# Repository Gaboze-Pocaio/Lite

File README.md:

# Gaboze Lite Edition
Gaboze Lite is an even more no frills version of the Game Boy Pocket and Raspberry Pi Zero.

## What Did We Do?

* [x] Lakka Only Release *(You Can Still Have RetroPie)*
* [x] TP4056 Module Removed for more efficient Texs Instruments
* [x] 5V Power Rail
* [x] Full USB OTG Support
* [x] New Button Library With Better Actuation
* [x] Two Buttons Only

## Why Did We Do This

Well, we slimmed it down to a two button build (you can always wire more on your own). After market evaluation, and to keep costs lower.

## Preview

| Top  | Bottom |
| ---- | ------ |
|      |        |

## More Soon
> Stay Up To Date

* [x] Be Sure To **Watch** This Repo
* [ ] Help Out By **Starring** This Repo

------
#### Buy Us A Coffee
> It's Not Mandatory, But Much [Appreciated](https://www.paypal.me/32teeth/1.99USD)

Everything we provide is free to use, Feedback is always welcome.

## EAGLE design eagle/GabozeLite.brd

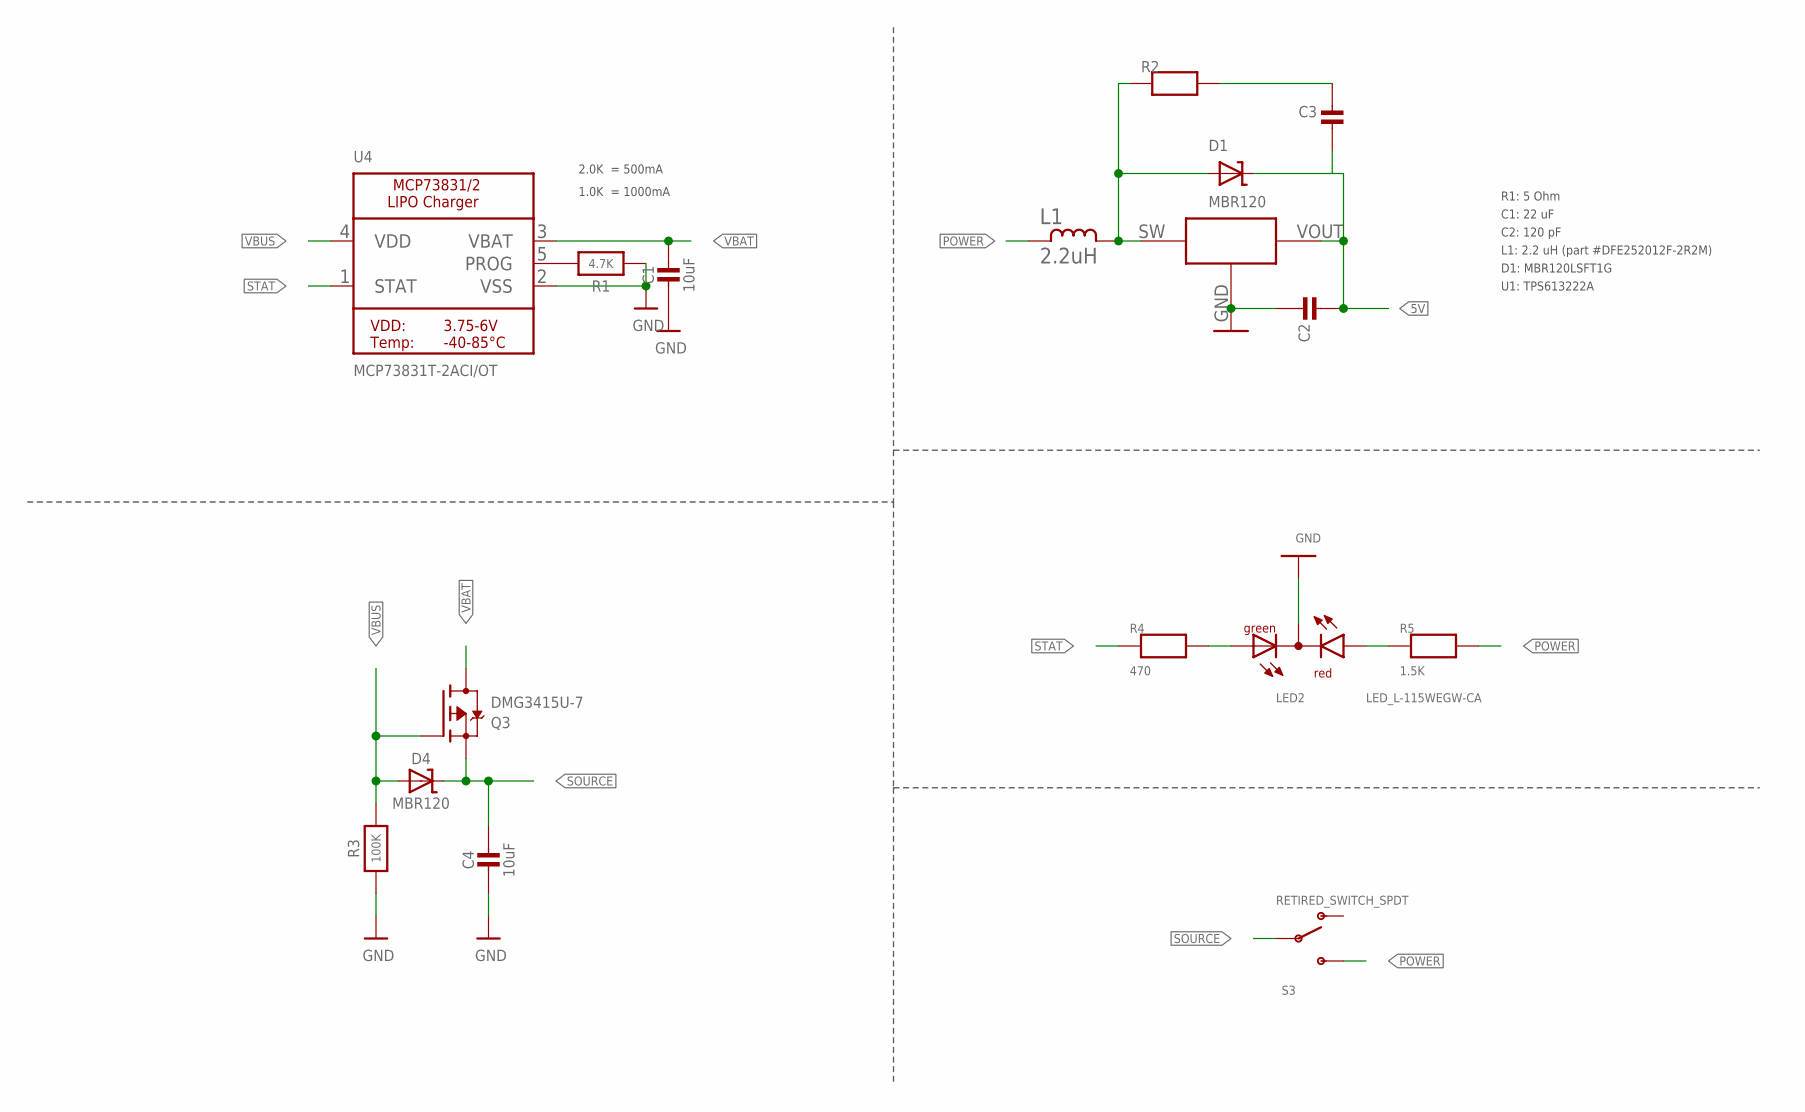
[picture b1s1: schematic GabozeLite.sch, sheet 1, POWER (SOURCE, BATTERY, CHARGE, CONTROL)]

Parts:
C1, C4: 10uF; 0603-MINI-CAP; MPN CL10A106MP8NNNC
C2: 22uf; 0603-MINI-CAP
C3: 120pf; 0603-MINI-CAP
D1, D4: MBR120; SOD-123; MPN MBR120LSFT1G
L1: 2.2uH; L1008CS
LED2: LED_L-115WEGW-CA; LED_DUOLED-A-3MM; MPN SSL-LX3059IGW
Q3: DMG3415U-7; SOT23-R; MPN DMG3415U-7
R1: 4.7K; 0603-MINI; MPN ERJ-PA3J472V
R2: 5Ohm; 0603-MINI
R3: 100K; 0603-MINI; MPN ERJ-PA3J104V
R4: 470; 0603-MINI; MPN ERJ-PA3J471V
R5: 1.5K; 0603-MINI; MPN ERJ-PA3J152V
S3: RETIRED_SWITCH_SPDT; RETIRED_KPS-1290; MPN RS-187R05A2-DS MT RT
U1: TPS613222A
U4: MCP73831T-2ACI/OT; SOT23-5-1; MPN MCP73831T-2ACI/OT

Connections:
5V: C2.2, C3.2, D1.C, U1.VOUT; also elsewhere on the board
GND: C1.2, C2.1, C4.2, LED2.2 (A), R1.1, R3.1, U1.GND, U4.2 (VSS); also elsewhere on the board
unnamed: D1.A, L1.2, R2.1, U1.SW
unnamed: C3.1, R2.2
POWER: L1.1, R5.2, S3.S
POWER_LED: LED2.3 (CR), R5.1
PROG: R1.2, U4.5 (PROG)
SOURCE: C4.1, D4.C, Q3.2 (S), S3.P
STAT: R4.1, U4.1 (STAT)
STAT_LED: LED2.1 (CG), R4.2
VBAT: C1.1, Q3.3 (D), U4.3 (VBAT); also elsewhere on the board
VBUS: D4.A, Q3.1 (G), R3.2, U4.4 (VDD); also elsewhere on the board

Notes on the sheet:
2.0K = 500mA
1.0K = 1000mA
R1: 5 Ohm C1: 22 uF C2: 120 pF L1: 2.2 uH (part #DFE252012F-2R2M) D1: MBR120LSFT1G U1: TPS613222A

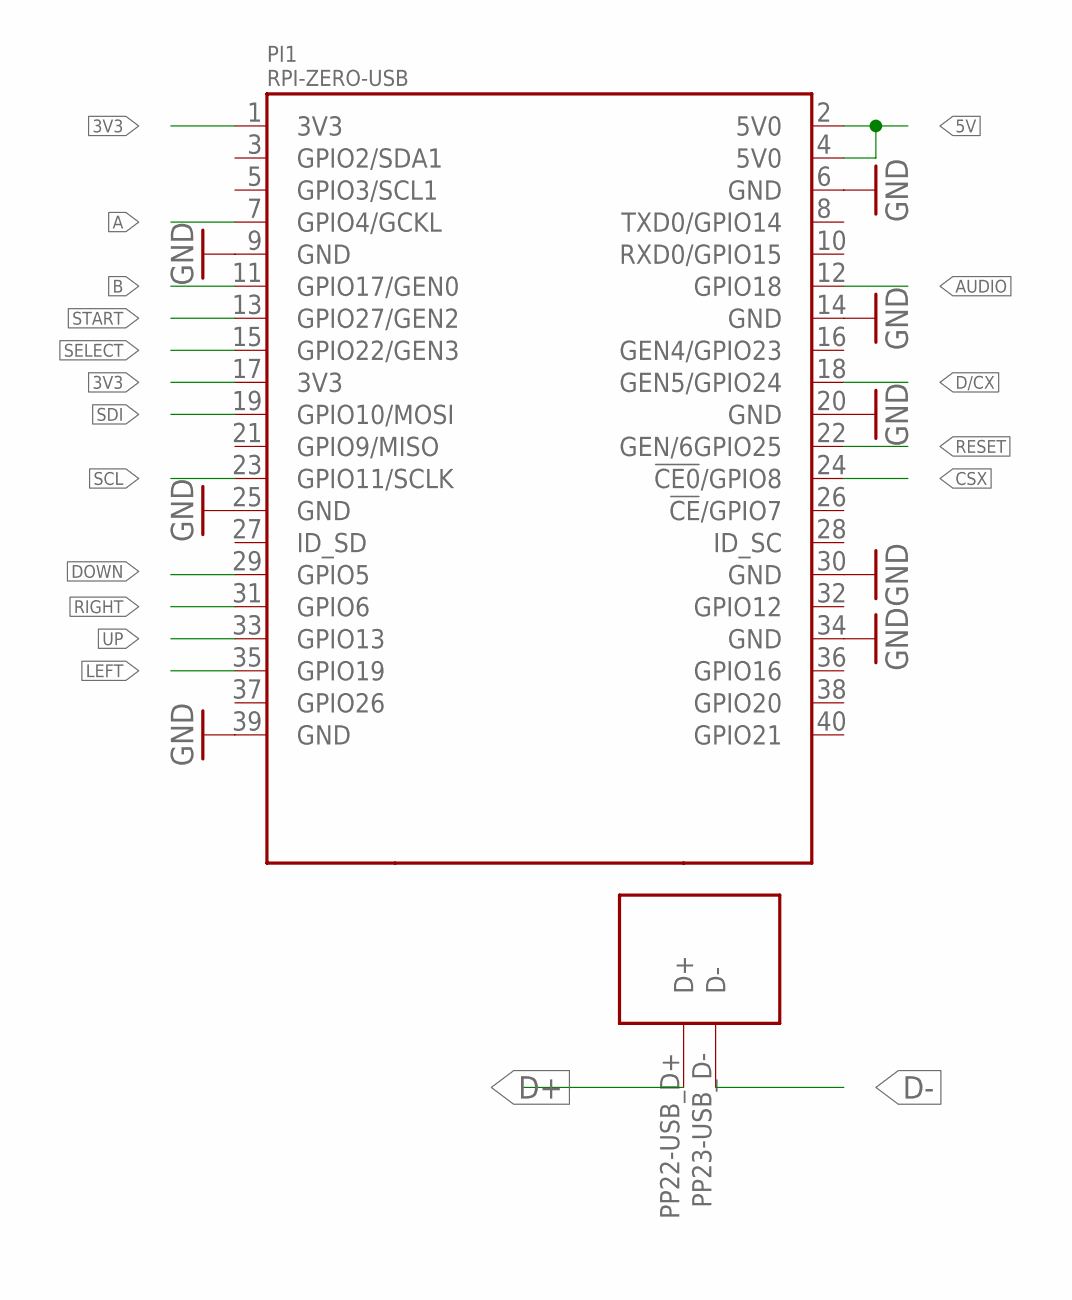
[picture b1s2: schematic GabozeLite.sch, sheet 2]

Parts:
PI1: RPI-ZERO-USB; RPI-ZERO-TH-USB-POGO

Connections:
3V3: PI1.1 (3V3), PI1.17 (3V3); also elsewhere on the board
5V: PI1.2 (5V0), PI1.4 (5V0); also elsewhere on the board
A: PI1.7 (GPIO4/GCKL); also elsewhere on the board
AUDIO: PI1.12 (GPIO18); also elsewhere on the board
B: PI1.11 (GPIO17/GEN0); also elsewhere on the board
CSX: PI1.24 (!CE0!/GPIO8); also elsewhere on the board
D+: PI1.PP22-USB_D+ (D+); also elsewhere on the board
D-: PI1.PP23-USB_D- (D-); also elsewhere on the board
D/CX: PI1.18 (GEN5/GPIO24); also elsewhere on the board
DOWN: PI1.29 (GPIO5); also elsewhere on the board
GND: PI1.6 (GND), PI1.9 (GND), PI1.14 (GND), PI1.20 (GND), PI1.25 (GND), PI1.30 (GND), PI1.34 (GND), PI1.39 (GND); also elsewhere on the board
LEFT: PI1.35 (GPIO19); also elsewhere on the board
RESET: PI1.22 (GEN/6GPIO25); also elsewhere on the board
RIGHT: PI1.31 (GPIO6); also elsewhere on the board
SCL: PI1.23 (GPIO11/SCLK); also elsewhere on the board
SDI: PI1.19 (GPIO10/MOSI); also elsewhere on the board
SELECT: PI1.15 (GPIO22/GEN3); also elsewhere on the board
START: PI1.13 (GPIO27/GEN2); also elsewhere on the board
UP: PI1.33 (GPIO13); also elsewhere on the board

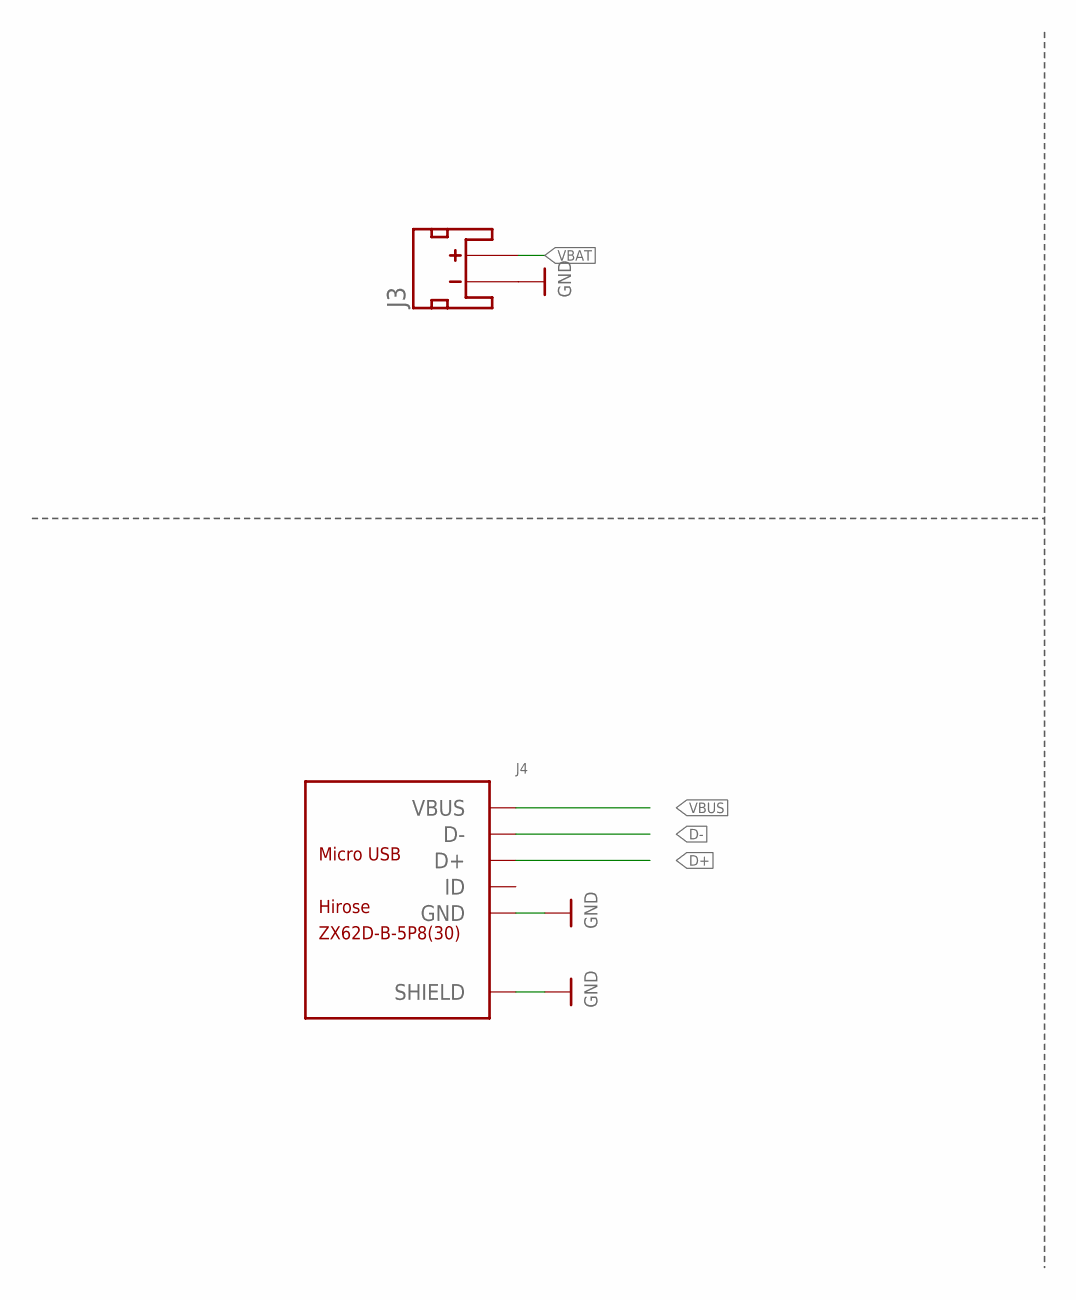
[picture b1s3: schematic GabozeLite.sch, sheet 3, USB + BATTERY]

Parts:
J3: Batt Conn; JST-2-SMD; MPN S2B-PH-SM4-TB(LF)(SN)
J4: ZX62D-B-5P8(30); MICRO-USB5+6P-SMD-0.65-AB

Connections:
D+: J4.3 (D+); also elsewhere on the board
D-: J4.2 (D-); also elsewhere on the board
GND: J3.1 (-), J4.5 (GND), J4.P1 (SHIELD), J4.P2 (SHIELD), J4.P3 (SHIELD), J4.P4 (SHIELD), J4.P5 (SHIELD), J4.P6 (SHIELD); also elsewhere on the board
VBAT: J3.2 (+); also elsewhere on the board
VBUS: J4.1 (VBUS); also elsewhere on the board

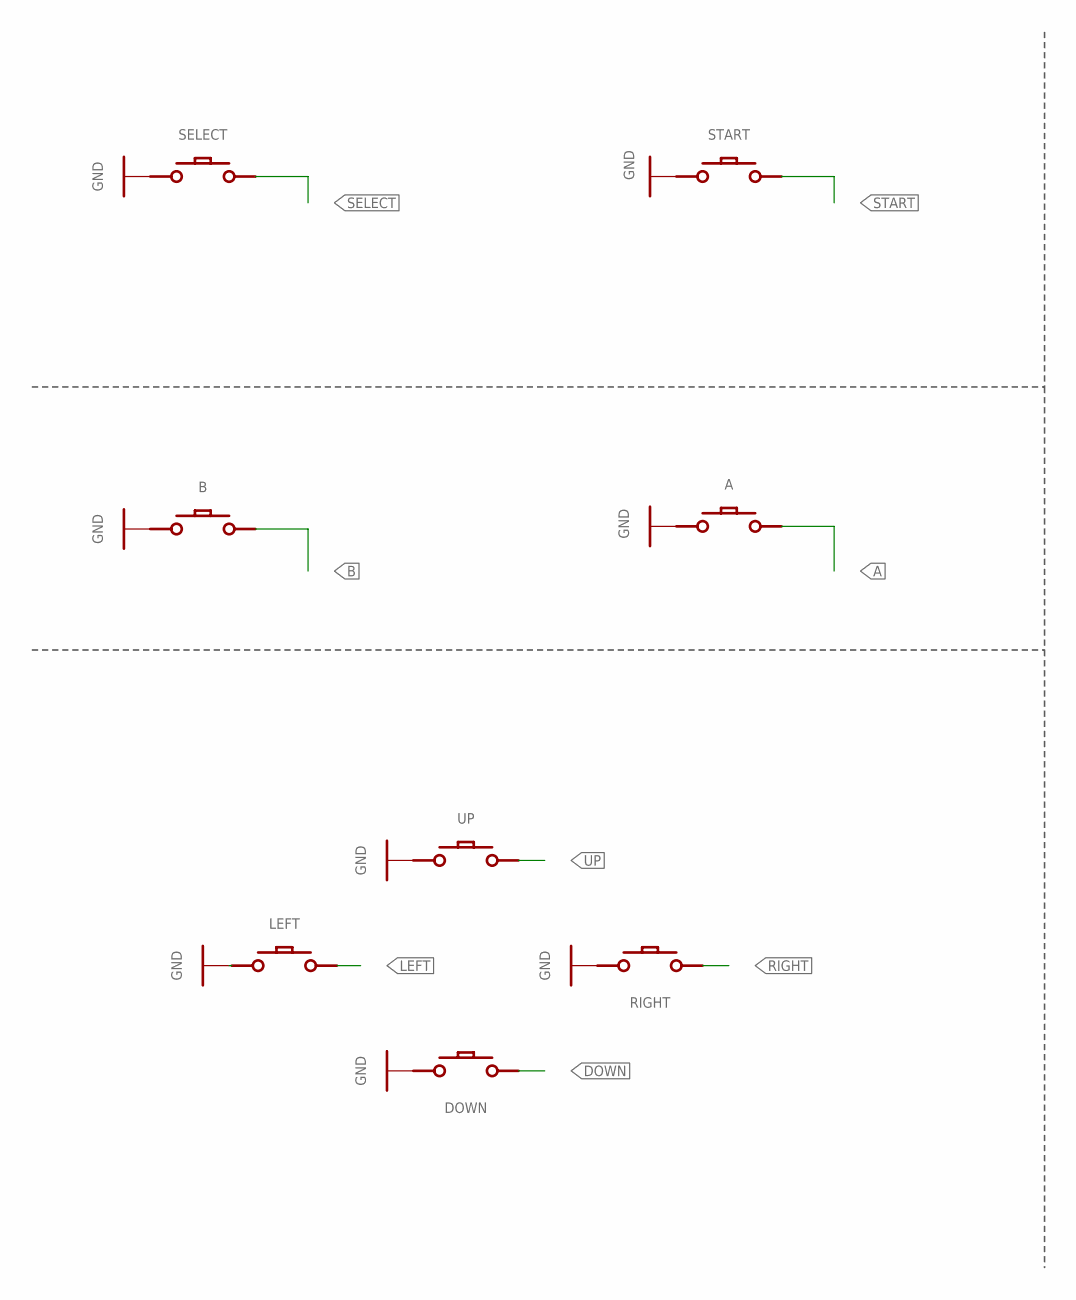
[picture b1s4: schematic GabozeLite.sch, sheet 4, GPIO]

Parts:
A: CONDUCTIVE_BUTTONCONDUCTIVE_BUTTON_THICK; CONDUCTIVE_BUTTON_THICK
B: CONDUCTIVE_BUTTONCONDUCTIVE_BUTTON_THICK; CONDUCTIVE_BUTTON_THICK
DOWN: CONDUCTIVE_BUTTONCONDUCTIVE_BUTTON_DIRECTIONAL_TH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; CONDUCTIVE_BUTTON_DIRECTIONAL_THICK
LEFT: CONDUCTIVE_BUTTONCONDUCTIVE_BUTTON_DIRECTIONAL_TH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; CONDUCTIVE_BUTTON_DIRECTIONAL_THICK
RIGHT: CONDUCTIVE_BUTTONCONDUCTIVE_BUTTON_DIRECTIONAL_TH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; CONDUCTIVE_BUTTON_DIRECTIONAL_THICK
SELECT: CONDUCTIVE_BUTTON_STARTSELECTCONDUCTIVE_BUTTON_TH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; CONDUCTIVE_BUTTON_THICK_STARTSELECT
START: CONDUCTIVE_BUTTON_STARTSELECTCONDUCTIVE_BUTTON_TH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; CONDUCTIVE_BUTTON_THICK_STARTSELECT
UP: CONDUCTIVE_BUTTONCONDUCTIVE_BUTTON_DIRECTIONAL_TH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; CONDUCTIVE_BUTTON_DIRECTIONAL_THICK

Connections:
A: A.P$ACTIVE; also elsewhere on the board
B: B.P$ACTIVE; also elsewhere on the board
DOWN: DOWN.P$ACTIVE; also elsewhere on the board
GND: A.P$GND, B.P$GND, DOWN.P$GND, LEFT.P$GND, RIGHT.P$GND, SELECT.P$GND, SELECT.P$GND1 (P$GND), SELECT.P$GND2 (P$GND), SELECT.P$GND3 (P$GND), START.P$GND, START.P$GND1 (P$GND), START.P$GND2 (P$GND), START.P$GND3 (P$GND), UP.P$GND; also elsewhere on the board
LEFT: LEFT.P$ACTIVE; also elsewhere on the board
RIGHT: RIGHT.P$ACTIVE; also elsewhere on the board
SELECT: SELECT.P$ACTIVE, SELECT.P$ACTIVE1 (P$ACTIVE), SELECT.P$ACTIVE2 (P$ACTIVE), SELECT.P$ACTIVE3 (P$ACTIVE), SELECT.P$ACTIVE4 (P$ACTIVE), SELECT.P$ACTIVE5 (P$ACTIVE), SELECT.P$ACTIVE6 (P$ACTIVE); also elsewhere on the board
START: START.P$ACTIVE, START.P$ACTIVE1 (P$ACTIVE), START.P$ACTIVE2 (P$ACTIVE), START.P$ACTIVE3 (P$ACTIVE), START.P$ACTIVE4 (P$ACTIVE), START.P$ACTIVE5 (P$ACTIVE), START.P$ACTIVE6 (P$ACTIVE); also elsewhere on the board
UP: UP.P$ACTIVE; also elsewhere on the board

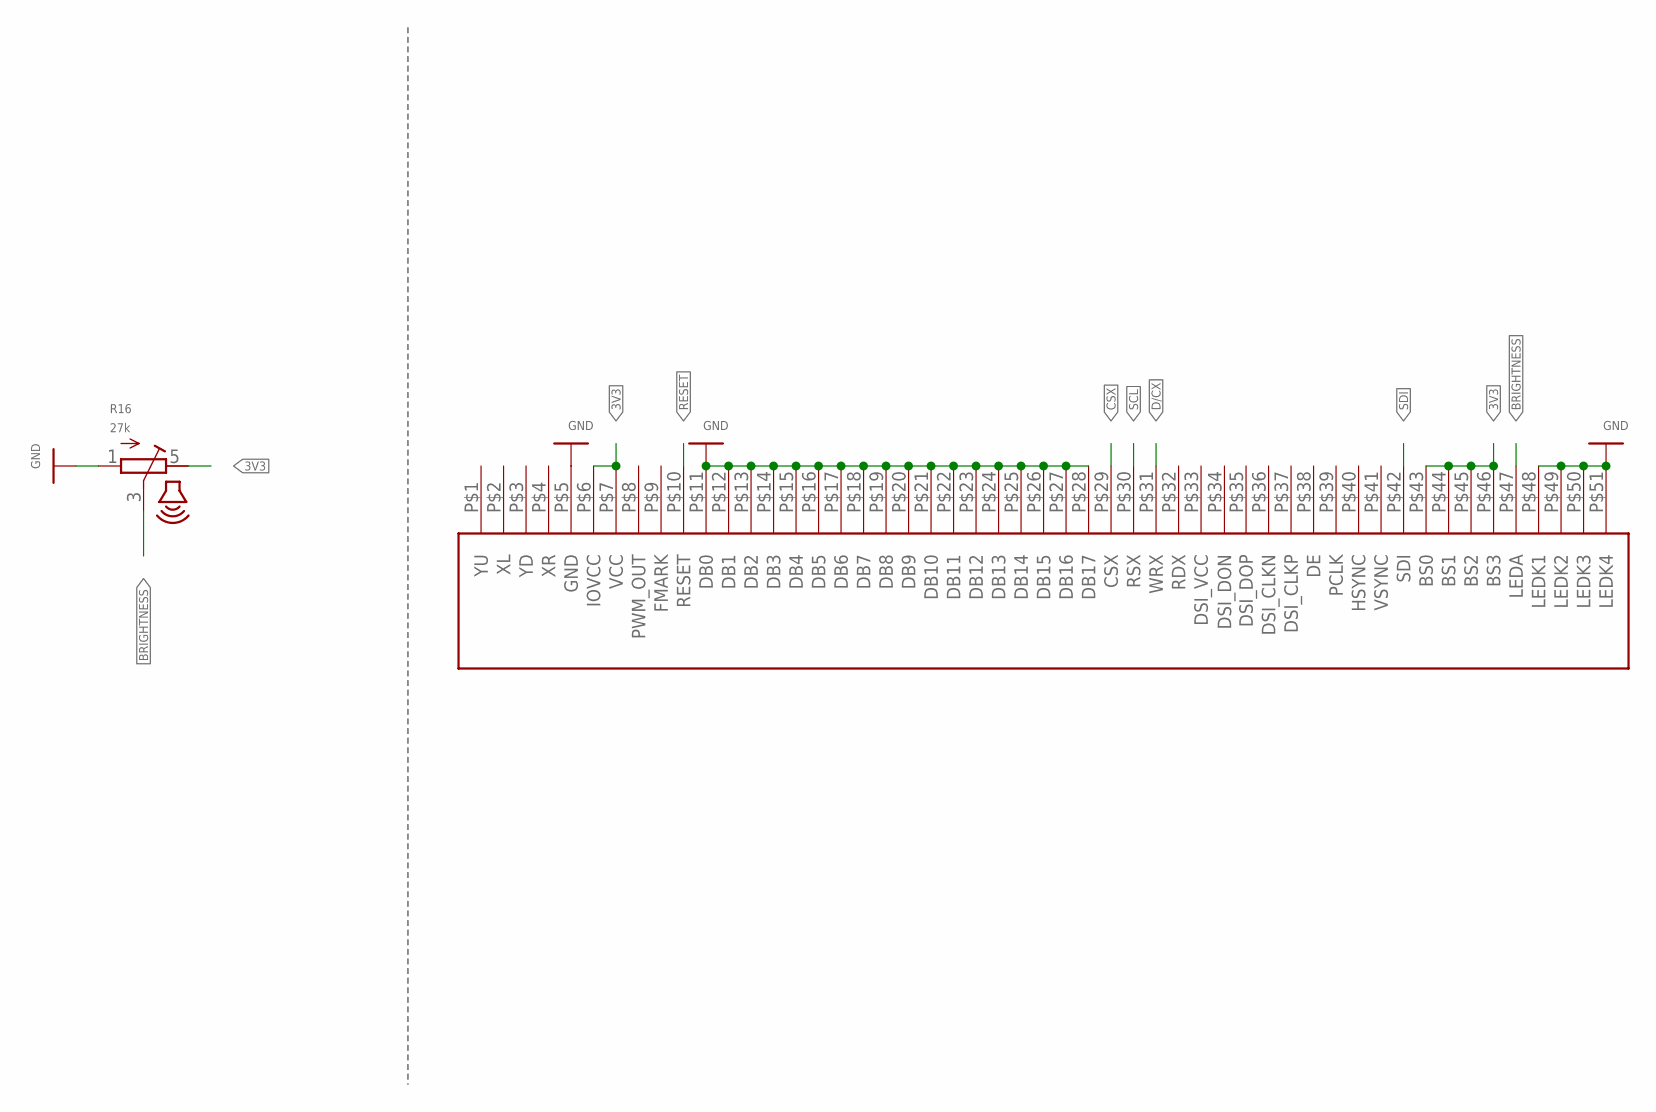
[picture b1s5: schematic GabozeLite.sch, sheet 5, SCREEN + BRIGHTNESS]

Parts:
R16: 27k; THUMBWHEEL
U5: ILI9342-2.6"

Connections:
3V3: R16.5 (E), U5.P$6 (IOVCC), U5.P$7 (VCC), U5.P$43 (BS0), U5.P$44 (BS1), U5.P$45 (BS2), U5.P$46 (BS3); also elsewhere on the board
BRIGHTNESS: R16.3 (S), U5.P$47 (LEDA)
CSX: U5.P$29 (CSX); also elsewhere on the board
D/CX: U5.P$31 (WRX); also elsewhere on the board
GND: R16.1 (A), U5.P$5 (GND), U5.P$11 (DB0), U5.P$12 (DB1), U5.P$13 (DB2), U5.P$14 (DB3), U5.P$15 (DB4), U5.P$16 (DB5), U5.P$17 (DB6), U5.P$18 (DB7), U5.P$19 (DB8), U5.P$20 (DB9), U5.P$21 (DB10), U5.P$22 (DB11), U5.P$23 (DB12), U5.P$24 (DB13), U5.P$25 (DB14), U5.P$26 (DB15), U5.P$27 (DB16), U5.P$28 (DB17), U5.P$48 (LEDK1), U5.P$49 (LEDK2), U5.P$50 (LEDK3), U5.P$51 (LEDK4); also elsewhere on the board
RESET: U5.P$10 (RESET); also elsewhere on the board
SCL: U5.P$30 (RSX); also elsewhere on the board
SDI: U5.P$42 (SDI); also elsewhere on the board

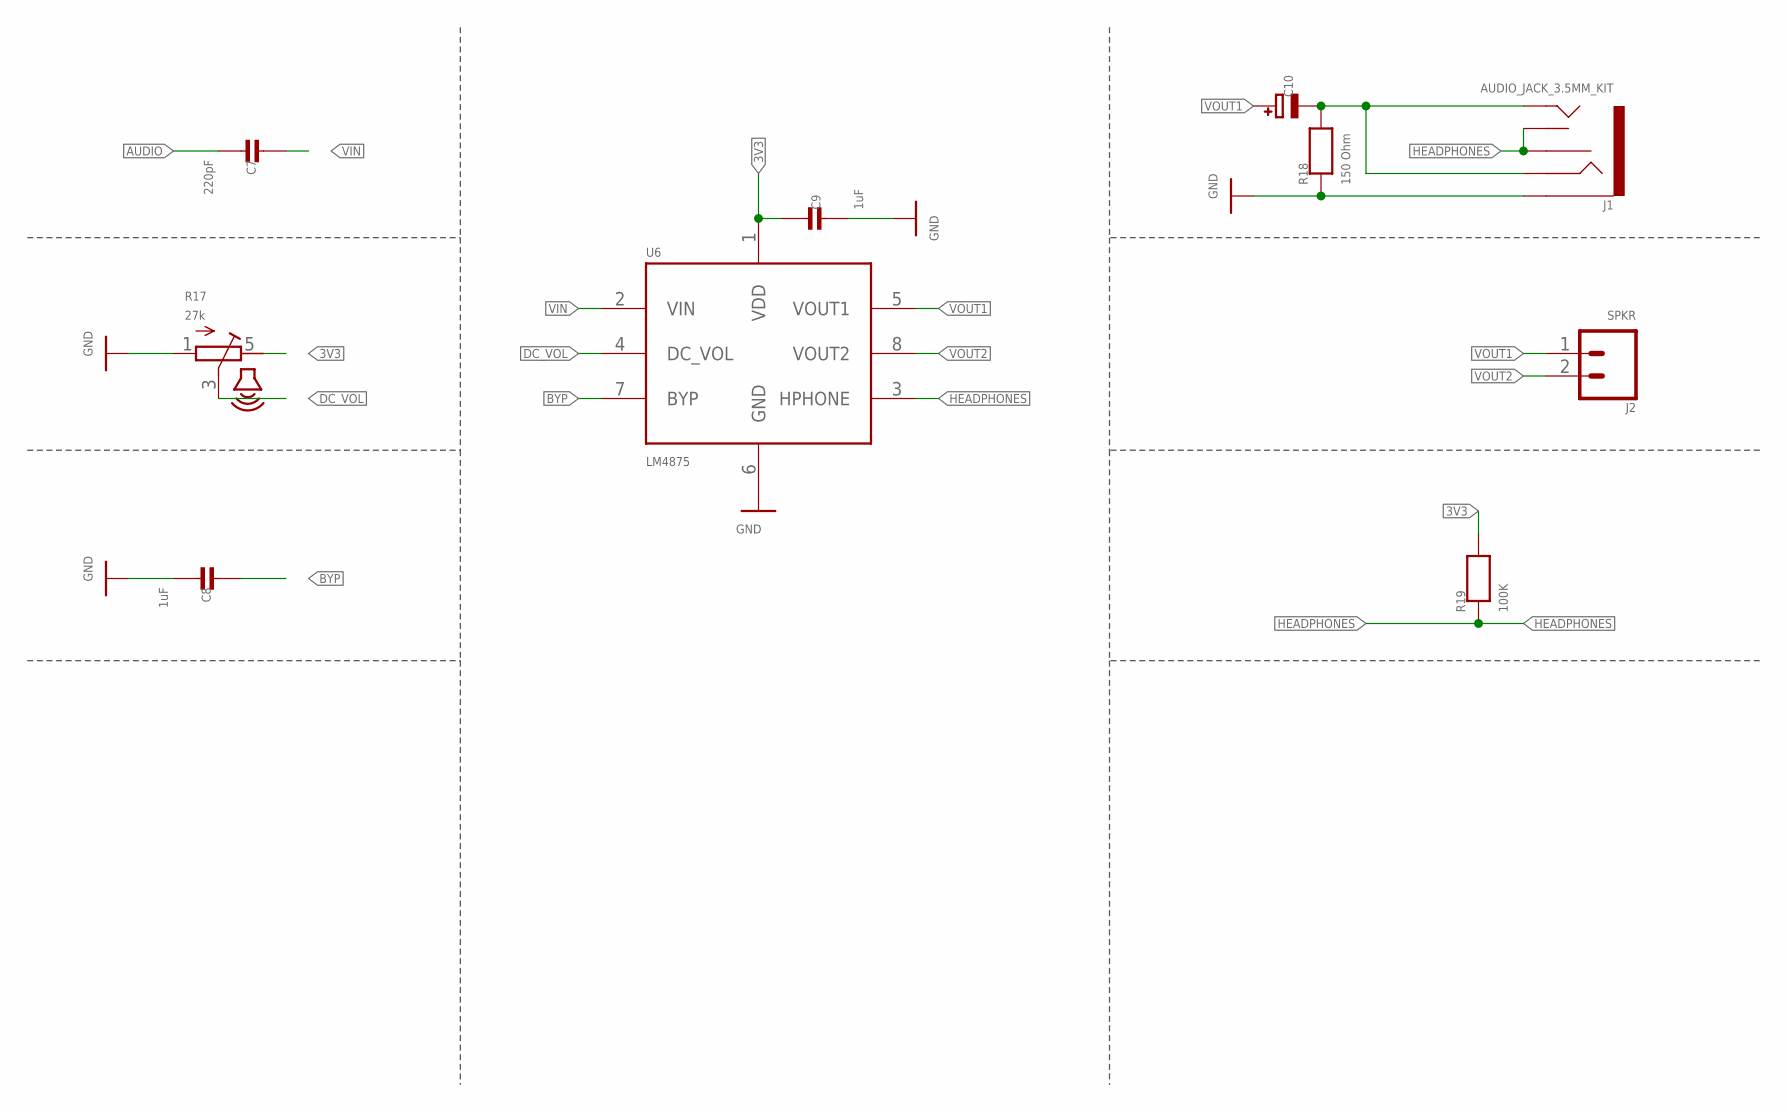
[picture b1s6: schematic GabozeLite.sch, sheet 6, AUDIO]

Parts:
C7: 220pF; 0603-MINI-CAP; MPN CL10C221JB8NNNC
C8, C9: 1uF; 0603-MINI-CAP; MPN CL10A105KP8NNNC
C10: 100uF; EIA3216-18/A-W; MPN 6TPH100MAEA
J1: AUDIO_JACK_3.5MM_KIT; AUDIO-JACK-KIT; MPN SJ1-3525NG-GR
J2: SPKR; 1X02
R17: 27k; THUMBWHEEL
R18: 150 Ohm; 0603-MINI; MPN ERJ-PA3J151V
R19: 100K; 0603-MINI; MPN ERJ-PA3J104V
U6: LM4875; SOIC8; MPN LM4875M/NOPB

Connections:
3V3: C9.1, R17.5 (E), R19.2, U6.1 (VDD); also elsewhere on the board
AUDIO: C7.2; also elsewhere on the board
BYP: C8.1, U6.7 (BYP)
DC_VOL: R17.3 (S), U6.4 (DC_VOL)
GND: C8.2, C9.2, J1.SLEEVE, R17.1 (A), R18.1, U6.6 (GND); also elsewhere on the board
HEADPHONES: J1.RSH, J1.TSH, R19.1, U6.3 (HPHONE)
VIN: C7.1, U6.2 (VIN)
VIN1: C10.-, J1.RING, J1.TIP, R18.2
VOUT1: C10.+, J2.1, U6.5 (VOUT1)
VOUT2: J2.2, U6.8 (VOUT2)

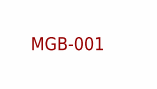
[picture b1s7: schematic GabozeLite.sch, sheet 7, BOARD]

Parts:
U$1: MGB-001

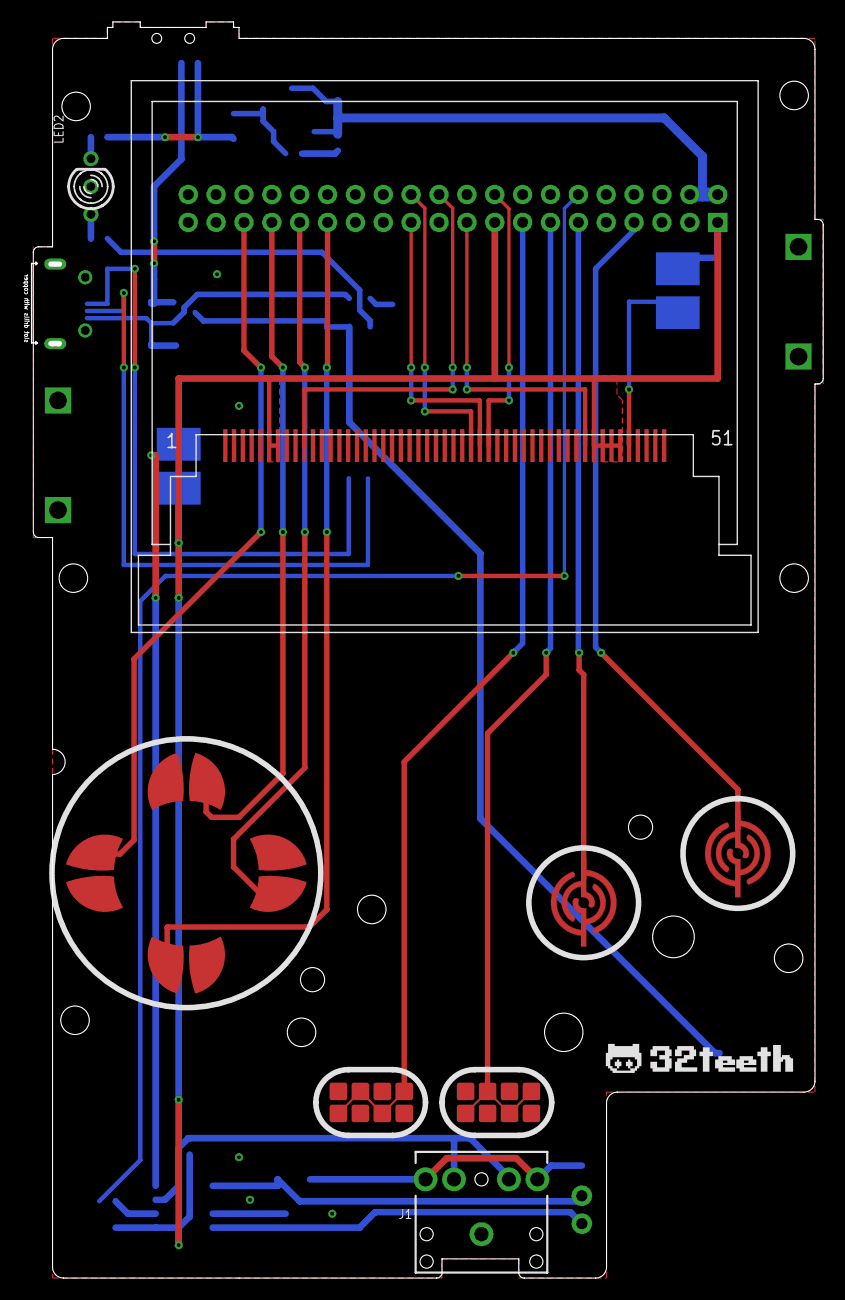
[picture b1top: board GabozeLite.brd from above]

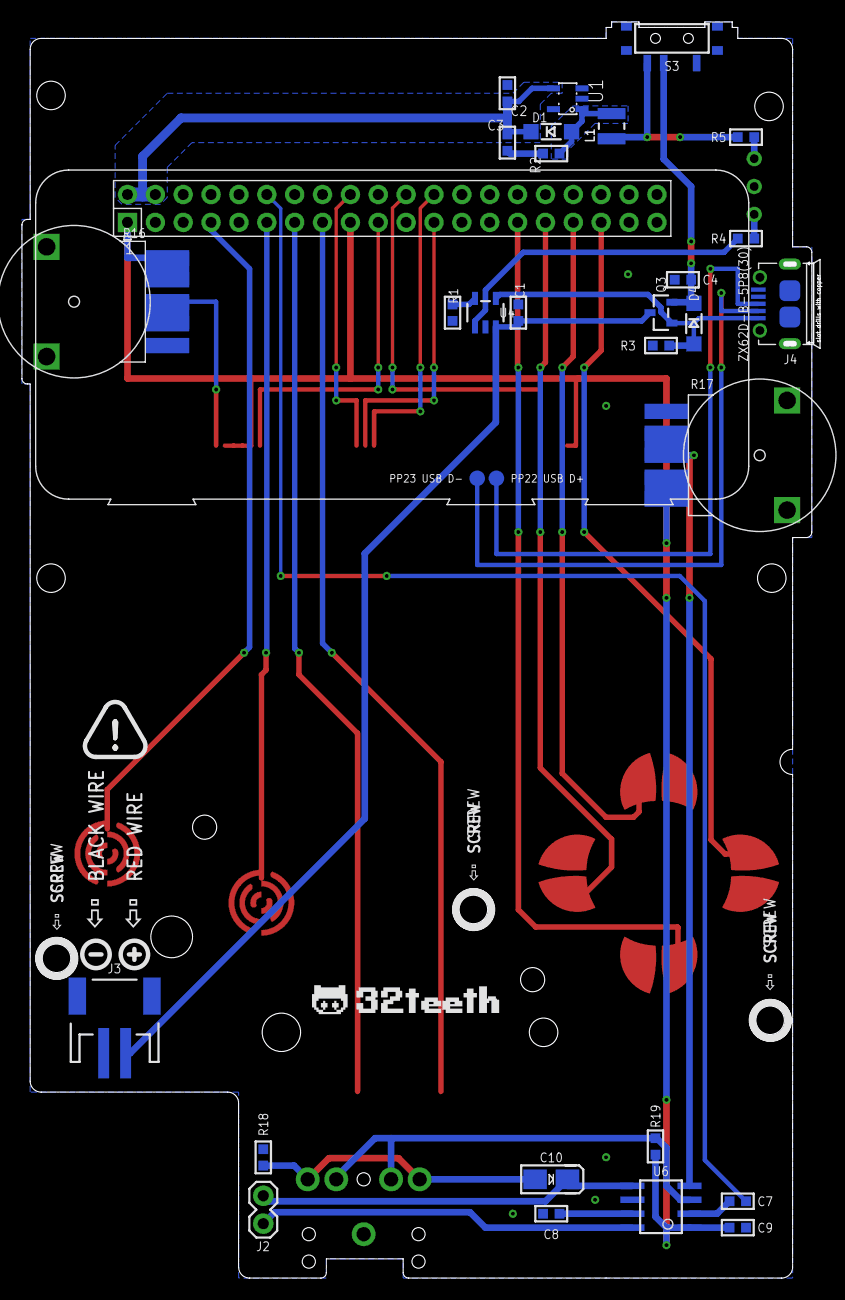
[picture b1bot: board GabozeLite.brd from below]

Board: 2 copper layers, 72.5 x 114.0 mm, 41 parts (29 on the bottom side), 37 nets.

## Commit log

2019-08-23 Fri 23 Aug 2019 16:51:22 EDT - Initial Commit
2019-08-23 Fri 23 Aug 2019 16:52:56 EDT - Initial Commit
2019-08-23 Fri 23 Aug 2019 16:57:01 EDT - Initial Commit
2019-08-23 Fri 23 Aug 2019 17:05:46 EDT - Initial Commit
2019-08-23 Fri 23 Aug 2019 17:08:04 EDT - Initial Commit
2019-08-23 Fri 23 Aug 2019 17:10:44 EDT - Initial Commit
2019-11-07 Thu 7 Nov 2019 06:29:39 EST - added Gerber and BOM
2020-04-24 Fri 24 Apr 2020 18:03:15 EDT - add source .brd and .sch files for public consumption

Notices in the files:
parts and their libraries:
microbuilder: This work is placed in the public domain, and may be freely used for commercial and non-commercial work with the following conditions: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
SparkFun-Aesthetics: Licensing: Creative Commons ShareAlike 4.0 International - https://creativecommons.org/licenses/by-sa/4.0
